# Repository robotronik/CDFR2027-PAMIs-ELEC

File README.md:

# CDFR2027-PAMIs-ELEC

PCBs for Eurobot's 2027 SIMAs.

This repository contains the KiCad design files for the electronic boards developed for the Robotronik Eurobot 2027 project. It includes modular PCB projects for the robot control and processing architecture, centered around ESP32 WROOM S3-based hardware.

## Overview

The project is organized into separate board designs:

- `ControlBoard/` — main control electronics board and associated KiCad schematics/PCB
- `BrainBoard/` — brain board project and related documentation

## Current status

This repository is currently under active development. Schematics, layouts, and interfaces may evolve as the hardware design is refined and validated.

## Design workflow

- Open the KiCad project files (`*.kicad_pro`) in KiCad 8+
- Review schematics and PCB layout in the corresponding board folders
- Use the design files as the source of truth for revisions and manufacturing outputs

## Repository structure

```text
.
├── BrainBoard/
│   └── README.md
├── ControlBoard/
│   ├── CDFR2027-PAMIs-ELEC-control.kicad_pro
│   ├── CDFR2027-PAMIs-ELEC-control.kicad_sch
│   ├── CDFR2027-PAMIs-ELEC-control.kicad_pcb
│   ├── power.kicad_sch
│   ├── io.kicad_sch
│   ├── motors.kicad_sch
│   ├── actuators.kicad_sch
│   └── ...
├── README.md
└── LICENSE (if added later)
```

## Notes

This repo is intended for PCB development and hardware iteration for the 2027 Eurobot competition. Contributions, schematic updates, and board revisions should be tracked in the corresponding board folders.

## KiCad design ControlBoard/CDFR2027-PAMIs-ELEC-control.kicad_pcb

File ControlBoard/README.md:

# ControlBoard

The ControlBoard is the low-level power and motion board of the robot. It is responsible for drivetrain control, actuator command management, IO handling, and the electrical interfaces required to move and operate the robot reliably.

This board is the execution layer of the robot architecture: it receives commands from the BrainBoard and converts them into motion, switching, and actuator behavior.

## Role in the robot

The ControlBoard focuses on the physical actuation layer:

- Motor drive and motion control
- Actuator control and PWM management
- Power distribution and regulation
- Digital/analog I/O interfaces
- Safety and command routing from the brain layer

## Key areas covered

The KiCad project is structured around several functional blocks:

- `power.kicad_sch` — power input, regulation, and distribution
- `motors.kicad_sch` — drivetrain motor interfaces and driver electronics
- `actuators.kicad_sch` — actuator control and related outputs
- `io.kicad_sch` — general-purpose I/O and interfacing
- `CDFR2027-PAMIs-ELEC-control.kicad_sch` — main schematic integration

## Typical responsibilities

- Driving the robot's wheels and movement systems
- Controlling servos, actuators, and mechanism outputs
- Managing switching and I/O states
- Distributing power to the vehicle subsystems
- Translating commands from the higher-level strategy layer into real hardware actions

## Board purpose

This board handles the operational part of the robot, while the `BrainBoard` handles higher-level strategy and coordination.

## Related project

- `../BrainBoard/` — central strategic logic and robot intelligence
- `../README.md` — repository overview

## Status

In development.

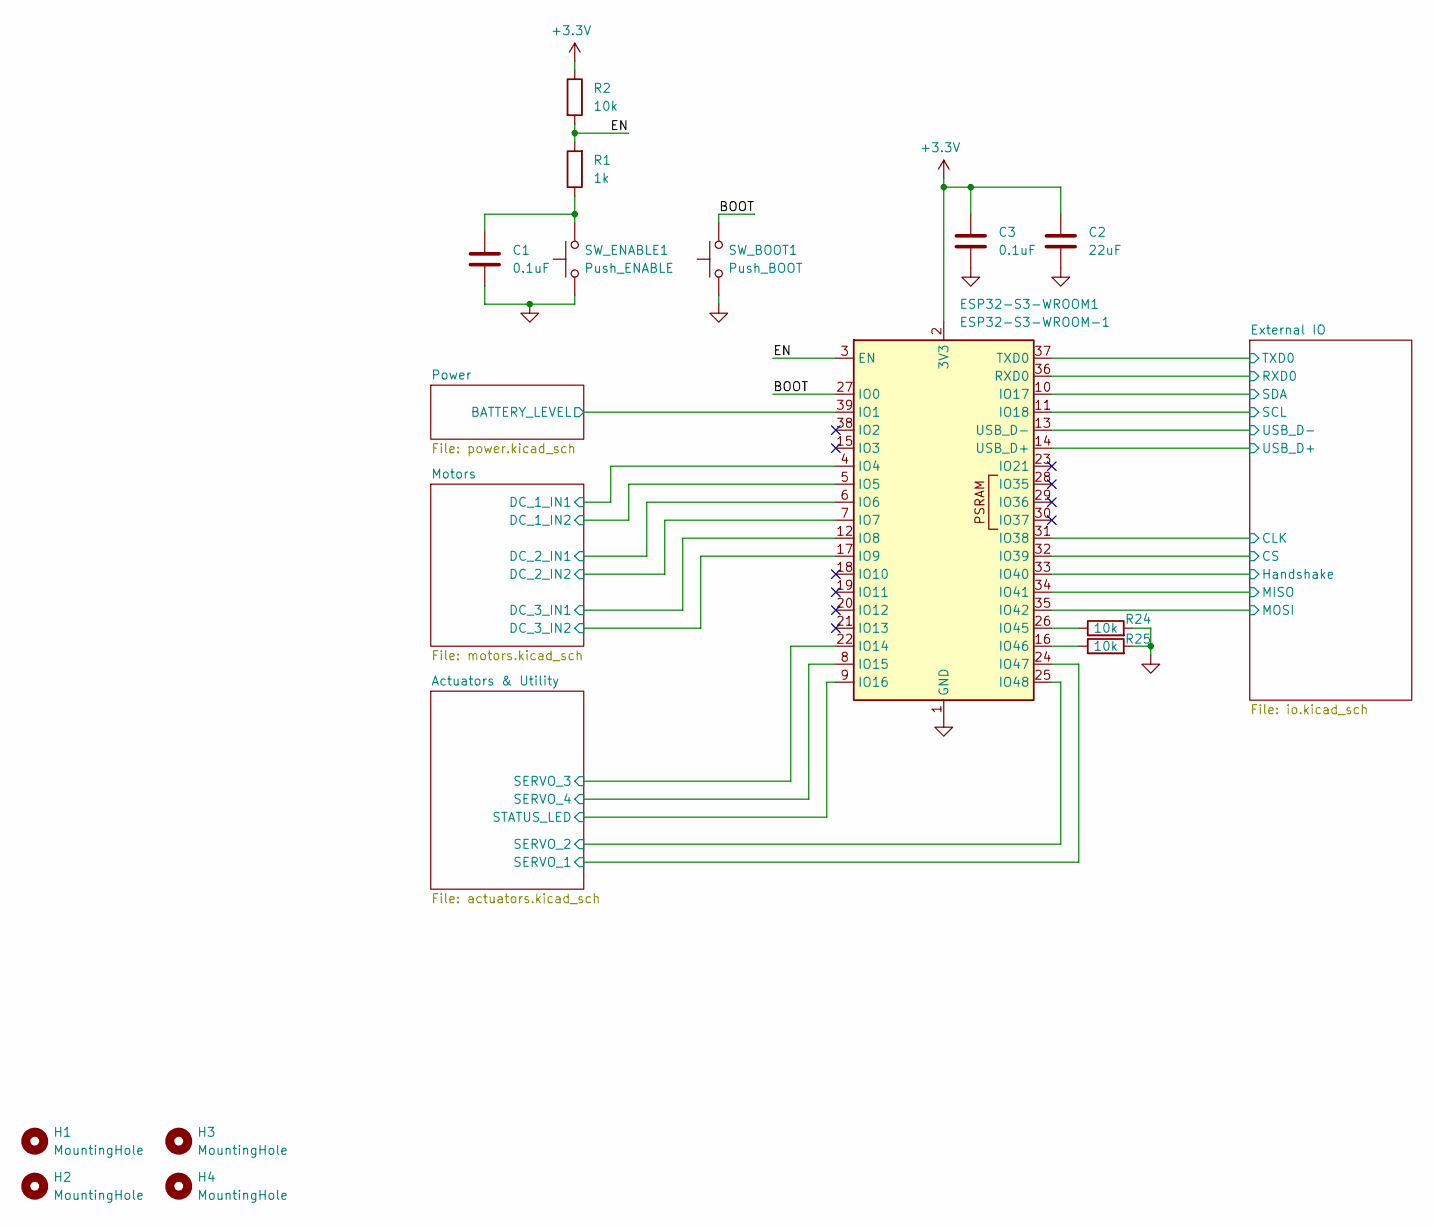
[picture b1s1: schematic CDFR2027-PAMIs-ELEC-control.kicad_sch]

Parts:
C1, C3: 0.1uF; C_0603_1608Metric; LCSC C1591
C2: 22uF; C_0603_1608Metric; LCSC C59461
ESP32-S3-WROOM1: ESP32-S3-WROOM-1; LCSC C3013946
H1, H2, H3, H4: MountingHole; MountingHole_3.2mm_M3
R1: 1k; R_0603_1608Metric; LCSC C22548
R2: 10k; R_0805_2012Metric; LCSC C84376
R24, R25: 10k; R_0603_1608Metric; LCSC C84376
SW_BOOT1: Push_BOOT; SW_PUSH_6mm; LCSC C55271357
SW_ENABLE1: Push_ENABLE; SW_PUSH_6mm; LCSC C55271357

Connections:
+3.3V: C2.2, C3.2, ESP32-S3-WROOM1.2 (3V3), R2.1; also elsewhere on the board
/Actuators & Utility/SERVO_1: ESP32-S3-WROOM1.24 (IO47); also elsewhere on the board
/Actuators & Utility/SERVO_2: ESP32-S3-WROOM1.25 (IO48); also elsewhere on the board
/Actuators & Utility/SERVO_3: ESP32-S3-WROOM1.22 (IO14); also elsewhere on the board
/Actuators & Utility/SERVO_4: ESP32-S3-WROOM1.8 (IO15); also elsewhere on the board
/Actuators & Utility/STATUS_LED: ESP32-S3-WROOM1.9 (IO16); also elsewhere on the board
/BOOT: ESP32-S3-WROOM1.27 (IO0), SW_BOOT1.2
/EN: ESP32-S3-WROOM1.3 (EN), R1.2, R2.2
/External IO/CLK: ESP32-S3-WROOM1.31 (IO38); also elsewhere on the board
/External IO/CS: ESP32-S3-WROOM1.32 (IO39); also elsewhere on the board
/External IO/Handshake: ESP32-S3-WROOM1.33 (IO40); also elsewhere on the board
/External IO/MISO: ESP32-S3-WROOM1.34 (IO41); also elsewhere on the board
/External IO/MOSI: ESP32-S3-WROOM1.35 (IO42); also elsewhere on the board
/External IO/RXD0: ESP32-S3-WROOM1.36 (RXD0); also elsewhere on the board
/External IO/SCL: ESP32-S3-WROOM1.11 (IO18); also elsewhere on the board
/External IO/SDA: ESP32-S3-WROOM1.10 (IO17); also elsewhere on the board
/External IO/TXD0: ESP32-S3-WROOM1.37 (TXD0); also elsewhere on the board
/External IO/USB_D+: ESP32-S3-WROOM1.14 (USB_D+); also elsewhere on the board
/External IO/USB_D-: ESP32-S3-WROOM1.13 (USB_D-); also elsewhere on the board
/Motors/DC_1_IN1: ESP32-S3-WROOM1.4 (IO4); also elsewhere on the board
/Motors/DC_1_IN2: ESP32-S3-WROOM1.5 (IO5); also elsewhere on the board
/Motors/DC_2_IN1: ESP32-S3-WROOM1.6 (IO6); also elsewhere on the board
/Motors/DC_2_IN2: ESP32-S3-WROOM1.7 (IO7); also elsewhere on the board
/Motors/DC_3_IN1: ESP32-S3-WROOM1.12 (IO8); also elsewhere on the board
/Motors/DC_3_IN2: ESP32-S3-WROOM1.17 (IO9); also elsewhere on the board
/Power/BATTERY_LEVEL: ESP32-S3-WROOM1.39 (IO1); also elsewhere on the board
GND: C1.1, C2.1, C3.1, ESP32-S3-WROOM1.1 (GND), ESP32-S3-WROOM1.40 (GND), ESP32-S3-WROOM1.41 (GND), R24.2, R25.2, SW_BOOT1.1, SW_ENABLE1.1; also elsewhere on the board
unnamed: C1.2, R1.1, SW_ENABLE1.2
unnamed: ESP32-S3-WROOM1.26 (IO45), R24.1
unnamed: ESP32-S3-WROOM1.16 (IO46), R25.1

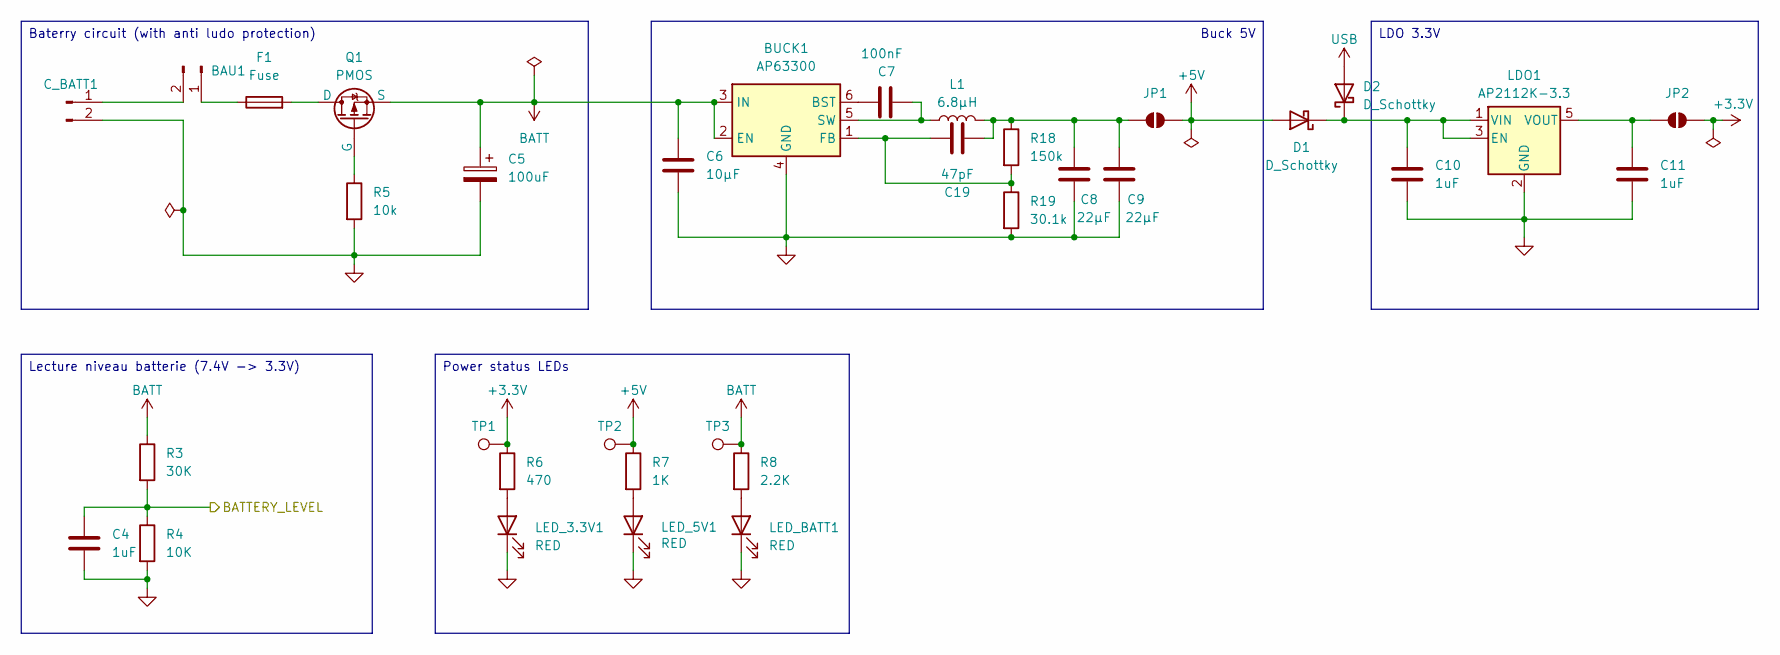
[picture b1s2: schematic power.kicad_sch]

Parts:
BAU1: Conn_01x02_Pin; AMASS_XT30U-M_1x02_P5.0mm_Vertical; LCSC C99102
BUCK1: AP63300; TSOT-23-6; LCSC C2158012
C4: 1uF; C_0603_1608Metric; LCSC C15849
C5: 100uF; CP_Elec_10x14.3; LCSC C48935390
C6: 10µF; C_0805_2012Metric; LCSC C15850
C7: 100nF; C_0805_2012Metric; LCSC C49678
C8, C9: 22µF; C_0805_2012Metric; LCSC C602037
C10, C11: 1uF; C_0603_1608Metric; LCSC C1592
C19: 47pF; C_0805_2012Metric; LCSC C107118
C_BATT1: Conn_01x02_Pin; AMASS_XT30U-M_1x02_P5.0mm_Vertical; LCSC C99102
D1, D2: D_Schottky; D_0603_1608Metric; LCSC C153761
F1: Fuse; Fuse_0603_1608Metric; LCSC C52988540
JP1, JP2: SolderJumper_2_Open; SolderJumper-2_P1.3mm_Open_RoundedPad1.0x1.5mm
L1: 6.8µH; L_Wurth_WE-LQSH-4020; LCSC C340380
LDO1: AP2112K-3.3; SOT-23-5; LCSC C51118
LED_3.3V1, LED_5V1: RED; LED_0603_1608Metric; LCSC C965799
LED_BATT1: RED; LED_0603_1608Metric; LCSC C965799
Q1: PMOS; SOT-223; LCSC C179617
R3: 30K; R_0603_1608Metric; LCSC C105575
R4: 10K; R_0603_1608Metric; LCSC C84376
R5: 10k; R_0805_2012Metric; LCSC C84376
R6: 470; R_0603_1608Metric; LCSC C441882
R7: 1K; R_0603_1608Metric; LCSC C22548
R8: 2.2K; R_0603_1608Metric; LCSC C114662
R18: 150k; R_0805_2012Metric; LCSC C2907299
R19: 30.1k; R_0805_2012Metric; LCSC C5184185
TP1, TP2, TP3: TestPoint; TestPoint_Pad_1.0x1.0mm

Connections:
+3.3V: JP2.2 (B), R6.1, TP1.1 (1_1); also elsewhere on the board
+5V: D1.2 (A), JP1.2 (B), R7.1, TP2.1 (1_1); also elsewhere on the board
/Power/BATTERY_LEVEL: C4.1, R3.2, R4.1; also elsewhere on the board
BATT: BUCK1.2 (EN), BUCK1.3 (IN), C5.1, C6.1, Q1.3 (S), R3.1, R8.1, TP3.1 (1_1); also elsewhere on the board
GND: BUCK1.4 (GND), C4.2, C5.2, C6.2, C8.2, C9.2, C10.2, C11.2, C_BATT1.2, LDO1.2 (GND), LED_3.3V1.1 (K), LED_5V1.1 (K), LED_BATT1.1 (K), R4.2, R5.2, R19.2; also elsewhere on the board
unnamed: BAU1.1, F1.1
unnamed: BAU1.2, C_BATT1.1
unnamed: BUCK1.6 (BST), C7.1
unnamed: BUCK1.1 (FB), C19.2, R18.2, R19.1
unnamed: BUCK1.5 (SW), C7.2, L1.1
unnamed: C10.1, D1.1 (K), D2.1 (K), LDO1.1 (VIN), LDO1.3 (EN)
unnamed: C8.1, C9.1, C19.1, JP1.1 (A), L1.2, R18.1
unnamed: C11.1, JP2.1 (A), LDO1.5 (VOUT)
unnamed: LED_3.3V1.2 (A), R6.2
unnamed: LED_5V1.2 (A), R7.2
unnamed: LED_BATT1.2 (A), R8.2
unnamed: F1.2, Q1.2 (D)
unnamed: Q1.1 (G), R5.1
USB: D2.2 (A); also elsewhere on the board

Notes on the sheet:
Baterry circuit (with anti ludo protection)
Buck 5V
Lecture niveau batterie (7.4V -> 3.3V)
LDO 3.3V
Power status LEDs

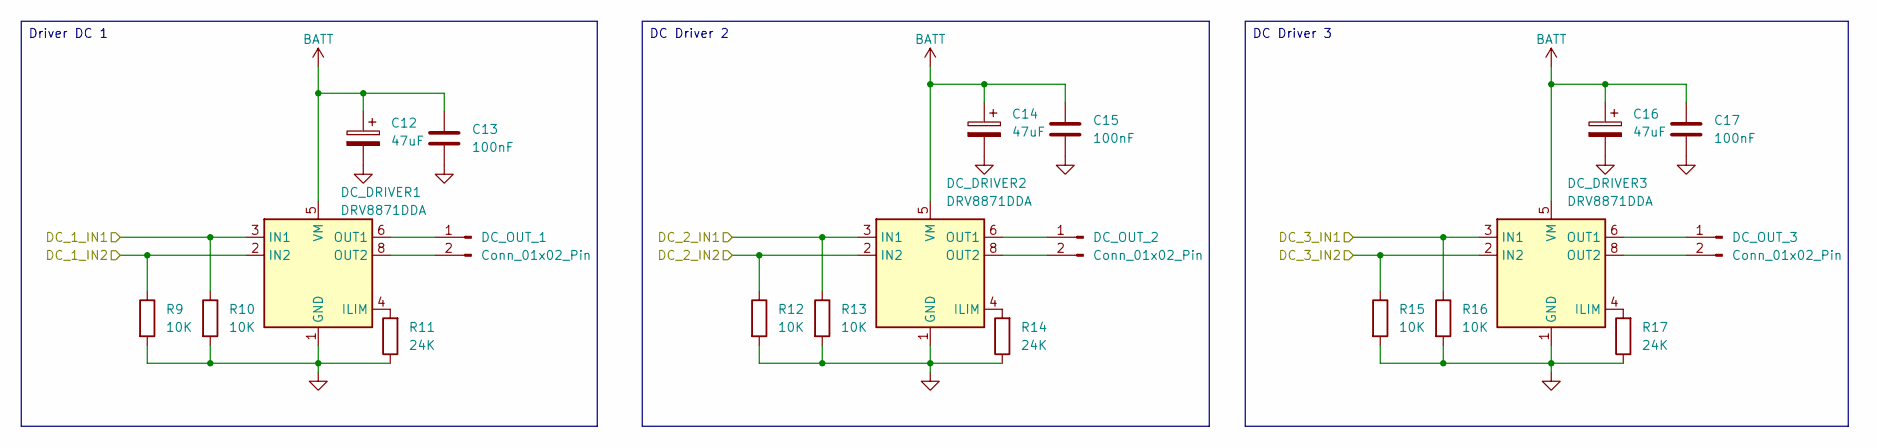
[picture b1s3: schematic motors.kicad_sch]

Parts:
C12, C14, C16: 47uF; Panasonic_F; LCSC C128464
C13, C15, C17: 100nF; C_0805_2012Metric; LCSC C49678
DC_DRIVER1, DC_DRIVER2, DC_DRIVER3: DRV8871DDA; Texas_HTSOP-8-1EP_3.9x4.9mm_P1.27mm_EP2.95x4.9mm_Mask2.4x3.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; LCSC C75864
DC_OUT_1, DC_OUT_2, DC_OUT_3: Conn_01x02_Pin; JST_XH_B2B-XH-A_1x02_P2.50mm_Vertical; LCSC C158012
R9, R10, R12, R13, R15, R16: 10K; R_0805_2012Metric; LCSC C17414
R11, R14, R17: 24K; R_0805_2012Metric; LCSC C2907246

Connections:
/Motors/DC_1_IN1: DC_DRIVER1.3 (IN1), R10.1; also elsewhere on the board
/Motors/DC_1_IN2: DC_DRIVER1.2 (IN2), R9.1; also elsewhere on the board
/Motors/DC_2_IN1: DC_DRIVER2.3 (IN1), R13.1; also elsewhere on the board
/Motors/DC_2_IN2: DC_DRIVER2.2 (IN2), R12.1; also elsewhere on the board
/Motors/DC_3_IN1: DC_DRIVER3.3 (IN1), R16.1; also elsewhere on the board
/Motors/DC_3_IN2: DC_DRIVER3.2 (IN2), R15.1; also elsewhere on the board
BATT: C12.1, C13.1, C14.1, C15.1, C16.1, C17.1, DC_DRIVER1.5 (VM), DC_DRIVER2.5 (VM), DC_DRIVER3.5 (VM); also elsewhere on the board
GND: C12.2, C13.2, C14.2, C15.2, C16.2, C17.2, DC_DRIVER1.1 (GND), DC_DRIVER1.7 (GND), DC_DRIVER1.9 (GND), DC_DRIVER2.1 (GND), DC_DRIVER2.7 (GND), DC_DRIVER2.9 (GND), DC_DRIVER3.1 (GND), DC_DRIVER3.7 (GND), DC_DRIVER3.9 (GND), R9.2, R10.2, R11.1, R12.2, R13.2, R14.1, R15.2, R16.2, R17.1; also elsewhere on the board
unnamed: DC_DRIVER1.4 (ILIM), R11.2
unnamed: DC_DRIVER1.6 (OUT1), DC_OUT_1.1
unnamed: DC_DRIVER1.8 (OUT2), DC_OUT_1.2
unnamed: DC_DRIVER2.4 (ILIM), R14.2
unnamed: DC_DRIVER2.6 (OUT1), DC_OUT_2.1
unnamed: DC_DRIVER2.8 (OUT2), DC_OUT_2.2
unnamed: DC_DRIVER3.4 (ILIM), R17.2
unnamed: DC_DRIVER3.6 (OUT1), DC_OUT_3.1
unnamed: DC_DRIVER3.8 (OUT2), DC_OUT_3.2

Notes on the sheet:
DC Driver 2
DC Driver 3
Driver DC 1

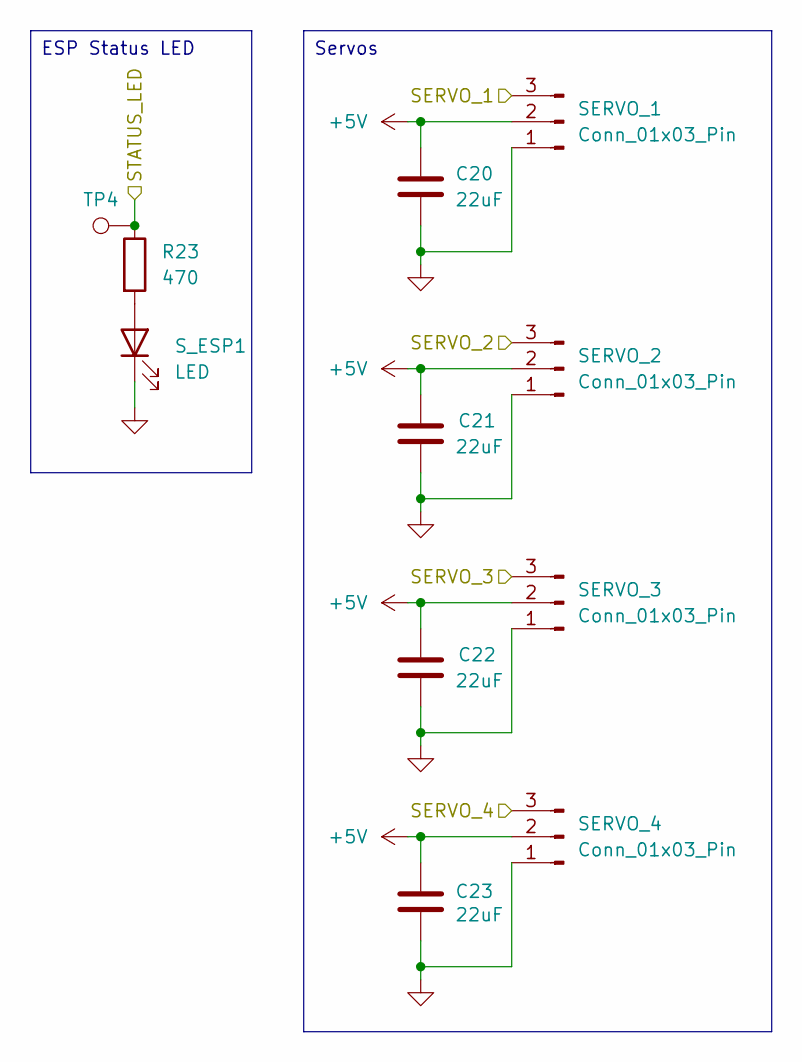
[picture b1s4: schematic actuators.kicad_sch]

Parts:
C20, C21, C22, C23: 22uF; C_0805_2012Metric
R23: 470; R_0603_1608Metric; LCSC C441882
SERVO_1, SERVO_2, SERVO_3, SERVO_4: Conn_01x03_Pin; JST_XH_B3B-XH-A_1x03_P2.50mm_Vertical; LCSC C144394
S_ESP1: LED; LED_0603_1608Metric; LCSC C965799
TP4: TestPoint; TestPoint_Pad_1.0x1.0mm

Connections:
+5V: C20.1, C21.1, C22.1, C23.1, SERVO_1.2, SERVO_2.2, SERVO_3.2, SERVO_4.2; also elsewhere on the board
/Actuators & Utility/SERVO_1: SERVO_1.3; also elsewhere on the board
/Actuators & Utility/SERVO_2: SERVO_2.3; also elsewhere on the board
/Actuators & Utility/SERVO_3: SERVO_3.3; also elsewhere on the board
/Actuators & Utility/SERVO_4: SERVO_4.3; also elsewhere on the board
/Actuators & Utility/STATUS_LED: R23.1, TP4.1 (1_1); also elsewhere on the board
GND: C20.2, C21.2, C22.2, C23.2, SERVO_1.1, SERVO_2.1, SERVO_3.1, SERVO_4.1, S_ESP1.1 (K); also elsewhere on the board
unnamed: R23.2, S_ESP1.2 (A)

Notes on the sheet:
ESP Status LED
Servos

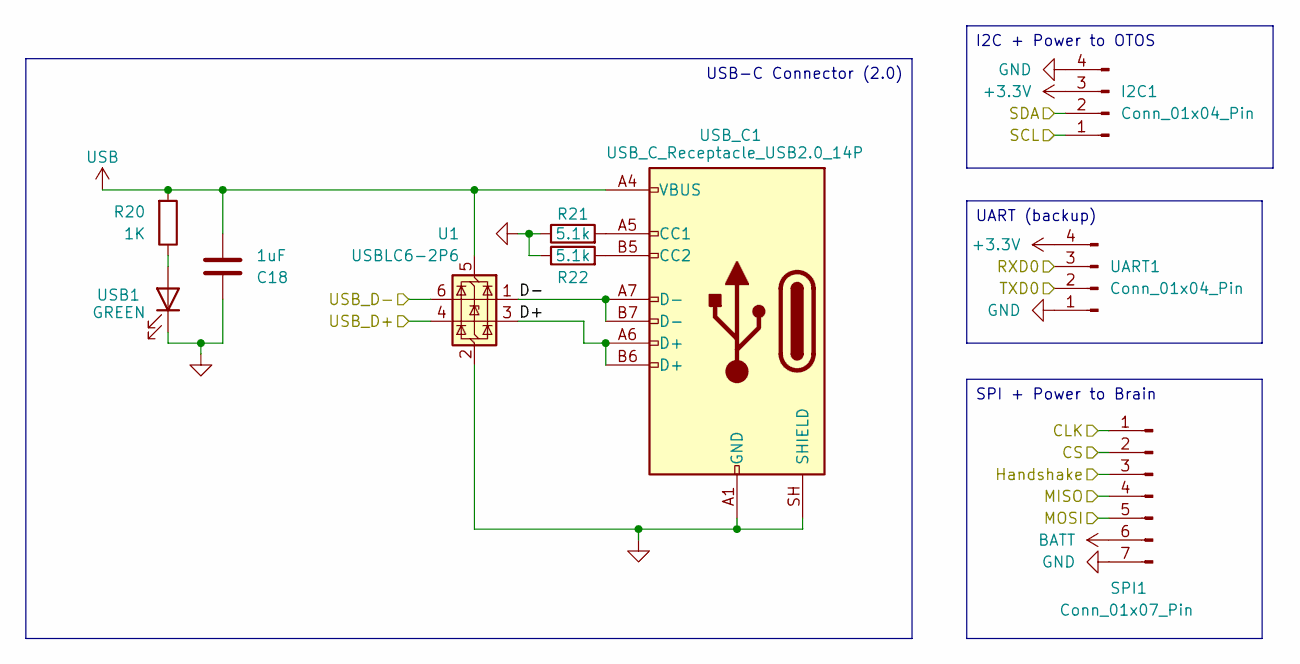
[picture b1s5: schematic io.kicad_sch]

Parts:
C18: 1uF; C_0603_1608Metric; LCSC C1592
I2C1: Conn_01x04_Pin; JST_XH_B4B-XH-A_1x04_P2.50mm_Vertical; LCSC C144395
R20: 1K; R_0603_1608Metric; LCSC C22548
R21, R22: 5.1k; R_0603_1608Metric; LCSC C2907044
SPI1: Conn_01x07_Pin; JST_XH_B7B-XH-A_1x07_P2.50mm_Vertical; LCSC C144398
U1: USBLC6-2P6; SOT-666; LCSC C15999
UART1: Conn_01x04_Pin; PinHeader_1x04_P2.54mm_Vertical; LCSC C52016392
USB1: GREEN; D_0603_1608Metric; LCSC C22371297
USB_C1: USB_C_Receptacle_USB2.0_14P; USB_C_Receptacle_GCT_USB4105-xx-A_16P_TopMnt_Horizontal; LCSC C2765186

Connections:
+3.3V: I2C1.3, UART1.4; also elsewhere on the board
/External IO/CLK: SPI1.1; also elsewhere on the board
/External IO/CS: SPI1.2; also elsewhere on the board
/External IO/D+: U1.3 (I/O2), USB_C1.A6 (D+), USB_C1.B6 (D+)
/External IO/D-: U1.1 (I/O1), USB_C1.A7 (D-), USB_C1.B7 (D-)
/External IO/Handshake: SPI1.3; also elsewhere on the board
/External IO/MISO: SPI1.4; also elsewhere on the board
/External IO/MOSI: SPI1.5; also elsewhere on the board
/External IO/RXD0: UART1.3; also elsewhere on the board
/External IO/SCL: I2C1.1; also elsewhere on the board
/External IO/SDA: I2C1.2; also elsewhere on the board
/External IO/TXD0: UART1.2; also elsewhere on the board
/External IO/USB_D+: U1.4 (I/O2); also elsewhere on the board
/External IO/USB_D-: U1.6 (I/O1); also elsewhere on the board
BATT: SPI1.6; also elsewhere on the board
GND: C18.1, I2C1.4, R21.1, R22.1, SPI1.7, U1.2 (GND), UART1.1, USB1.1 (K), USB_C1.A1 (GND), USB_C1.A12 (GND), USB_C1.B1 (GND), USB_C1.B12 (GND), USB_C1.SH (SHIELD); also elsewhere on the board
unnamed: R20.1, USB1.2 (A)
unnamed: R21.2, USB_C1.A5 (CC1)
unnamed: R22.2, USB_C1.B5 (CC2)
USB: C18.2, R20.2, U1.5 (VBUS), USB_C1.A4 (VBUS), USB_C1.A9 (VBUS), USB_C1.B4 (VBUS), USB_C1.B9 (VBUS); also elsewhere on the board

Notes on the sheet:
UART (backup)
USB-C Connector (2.0)
I2C + Power to OTOS
SPI + Power to Brain

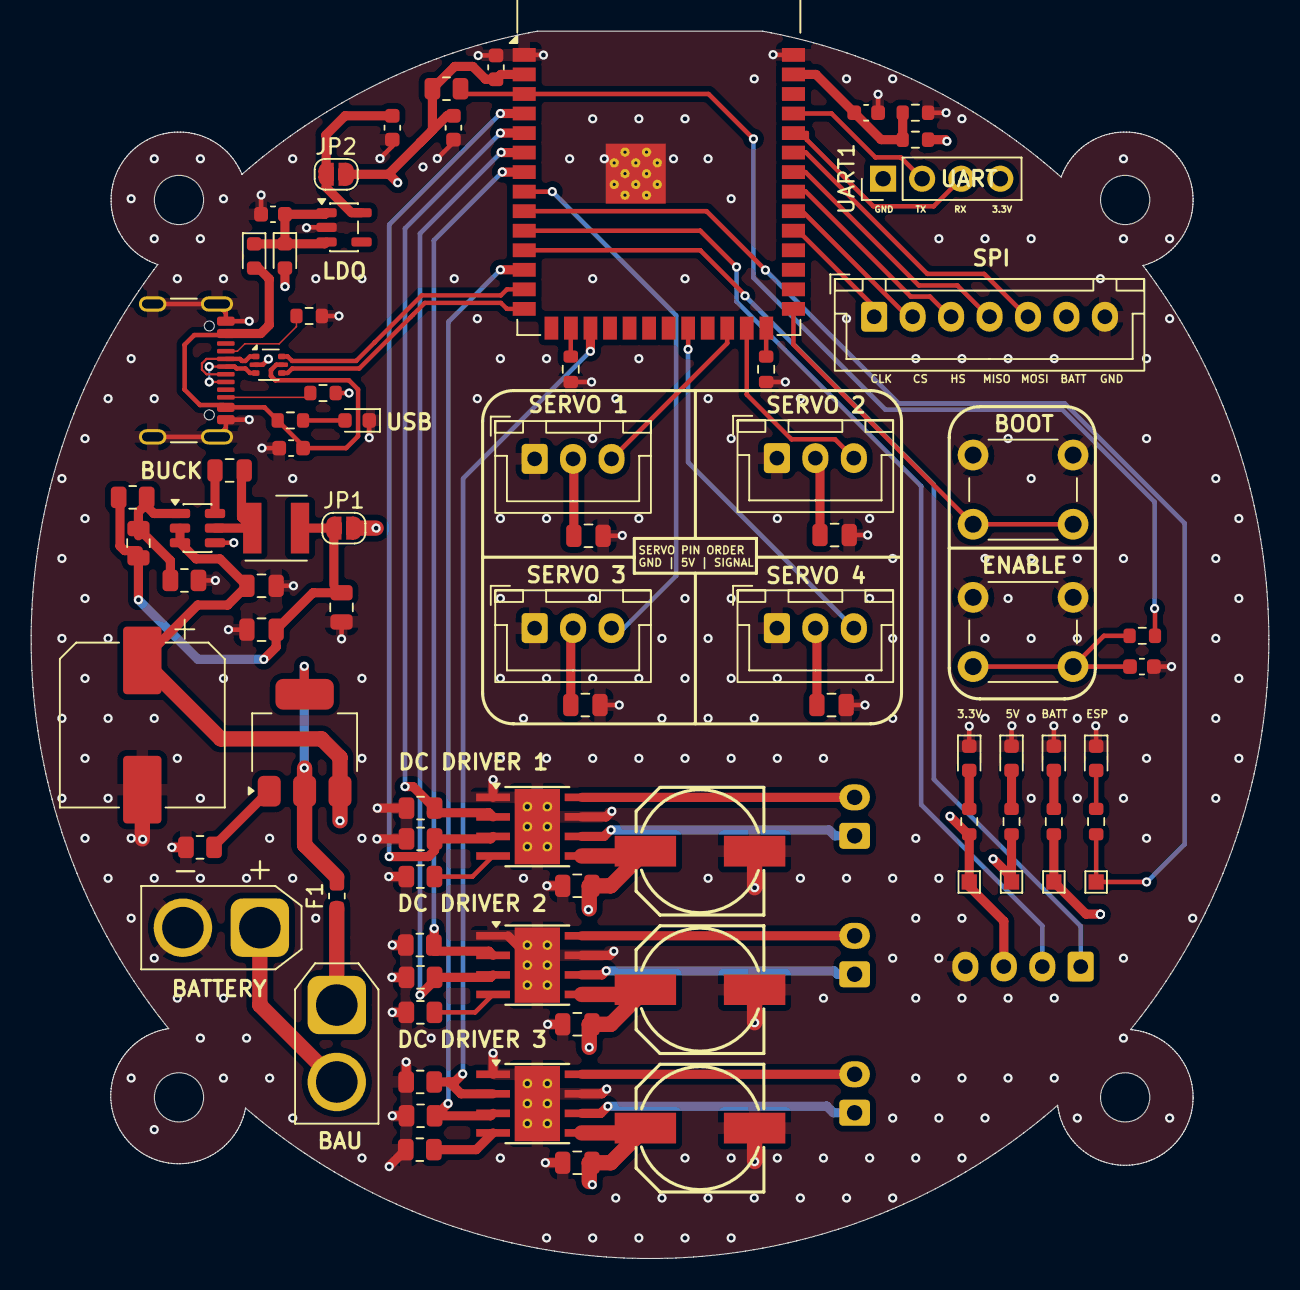
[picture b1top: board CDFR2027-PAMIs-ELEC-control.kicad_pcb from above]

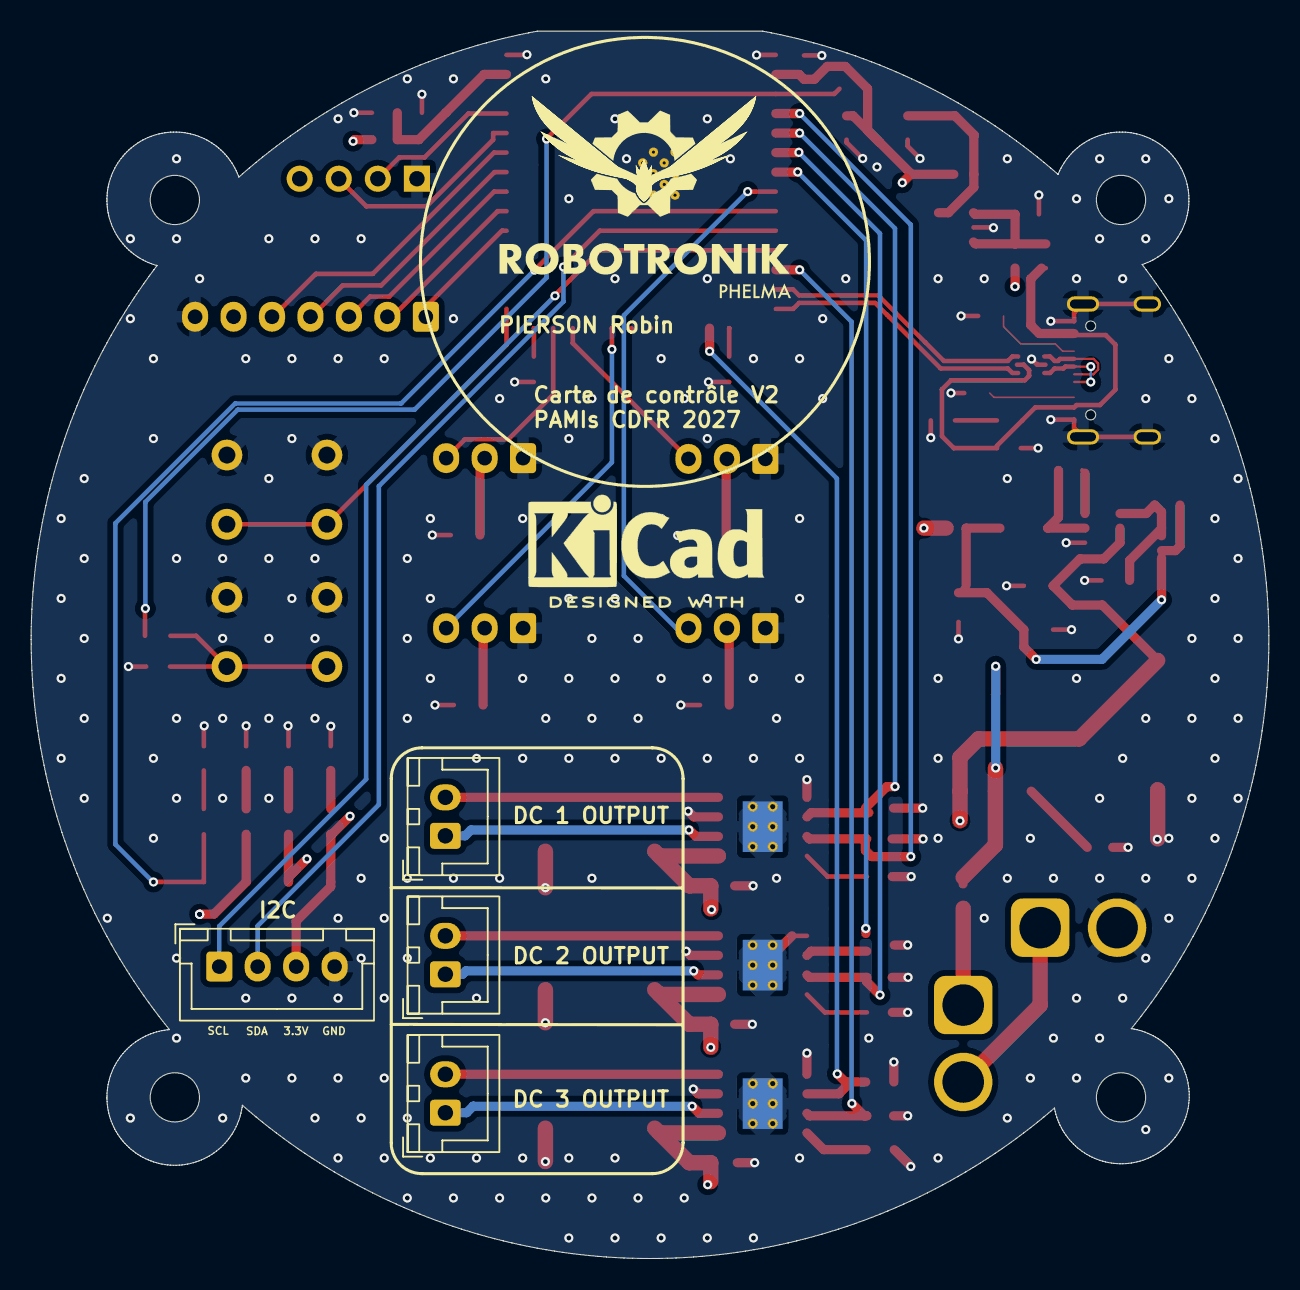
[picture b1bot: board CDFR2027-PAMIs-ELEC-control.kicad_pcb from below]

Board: 4 copper layers, 80.4 x 79.8 mm, 90 parts (4 on the bottom side), 61 nets.
